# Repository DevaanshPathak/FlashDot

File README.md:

# 🔦 FlashDot — Light-Controlled Morse Code Flasher

**FlashDot** is a simple analog circuit that lets you transmit Morse code using your hand and light. Wave your fingers over an LDR (photoresistor), and an LED blinks in response. It's tactile, visual, and powered by nothing but a transistor and your creativity.

This project was built for Hack Club’s [Solder Program](https://github.com/hackclub/solder)!

---

## ✨ What It Does

FlashDot reacts to light changes — when you cover the photoresistor, it flips on an NPN transistor, causing the LED to light up. With a single finger, you can tap out Morse code, send signals, or just vibe with light.

You can replace the LED with a vibration motor to make a **tactile flasher** too.

---

## 📦 Bill of Materials

| Component         | Quantity | Notes                             |
|------------------|----------|-----------------------------------|
| Photoresistor (LDR - GL5528) | 1 | Senses ambient light            |
| 2N3904 NPN Transistor         | 1 | Main switch                     |
| 220Ω Resistor                 | 1 | LED current limiting            |
| 47kΩ Resistor                 | 1 | Forms voltage divider with LDR |
| 10µF Electrolytic Capacitor   | 1 | Debounces fast flickers         |
| 5mm LED                       | 1 | Light output                    |
| CR2032 Coin Cell + Holder     | 1 | Power source                    |
| PCB / Breadboard              | 1 | Custom-designed PCB             |

---

## 📐 Circuit Design

### 🧠 Schematic

### 🧩 PCB Layout

### 🔭 3D View 1

### 🔬 3D View 2

### 3D View Back

> All files live in the `kicad/` and `gerbers/` folders.

---

## 🛠️ Files in This Repo

```

flashdot/
├── kicad/         → KiCad project, schematic, PCB layout
├── gerbers/       → Gerber + drill files (for fabrication)
├── imgs/          → Screenshots: schematic, PCB, 3D views
├── LICENSE        → MIT
└── README.md      → You’re here!

```

---

## 🧪 Testing It

Power the circuit using a coin cell.  
Then:
- ✅ Leave the LDR uncovered → LED stays off
- ✅ Cover the LDR briefly → LED blinks
- ✅ Try long and short covers → Manual Morse code!

---

## 🙋 Slack Username

Devaansh Pathak

U091678RUNB

---

## 🚀 Why I Made This

I wanted to make something dead simple, no microcontroller, no code — just light, your hand, and physics. FlashDot is my second analog PCB and my second time using KiCad. I learned about debounce circuits, transistor switching, and footprint alignment.

---

## 📎 License

MIT — remix, learn, and solder your own.

---

## 📣 Bonus Ideas

- Swap LED with motor for silent signaling
- Make it wearable with a coin cell backpack
- Add a potentiometer for adjustable sensitivity

---

Built for [Hack Club Solder](https://github.com/hackclub/solder) 💚

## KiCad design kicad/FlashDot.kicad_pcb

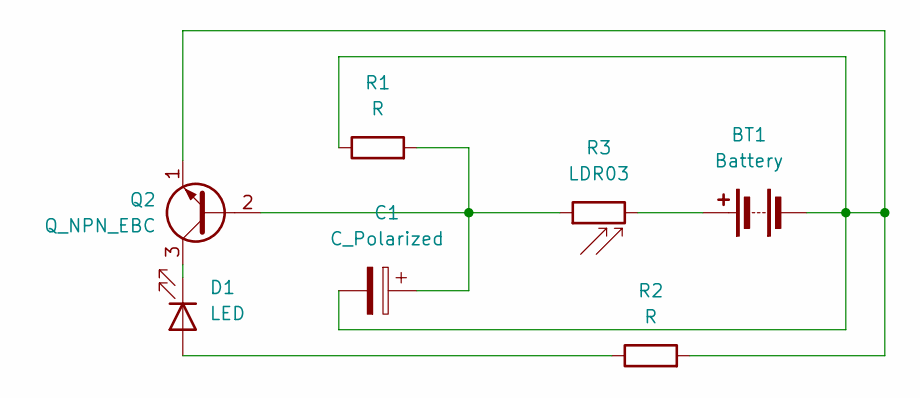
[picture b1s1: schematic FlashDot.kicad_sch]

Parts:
BT1: Battery; BatteryHolder_Keystone_3000_1x12mm
C1: C_Polarized; CP_Radial_D5.0mm_P2.00mm
D1: LED; LED_D5.0mm
Q2: Q_NPN_EBC; TO-92_Inline
R1, R2: R; R_Axial_DIN0207_L6.3mm_D2.5mm_P7.62mm_Horizontal
R3: LDR03; R_LDR_10x8.5mm_P7.6mm_Vertical

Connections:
unnamed: BT1.1 (+), R3.2
unnamed: BT1.2 (-), C1.2, Q2.1 (E), R1.1, R2.2
unnamed: D1.2 (A), R2.1
unnamed: D1.1 (K), Q2.3 (C)
unnamed: C1.1, Q2.2 (B), R1.2, R3.1

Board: 2 copper layers, 7 parts (0 on the bottom side), 5 nets, no tracks yet.

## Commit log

2025-06-19 Push Files
2025-06-20 Done
